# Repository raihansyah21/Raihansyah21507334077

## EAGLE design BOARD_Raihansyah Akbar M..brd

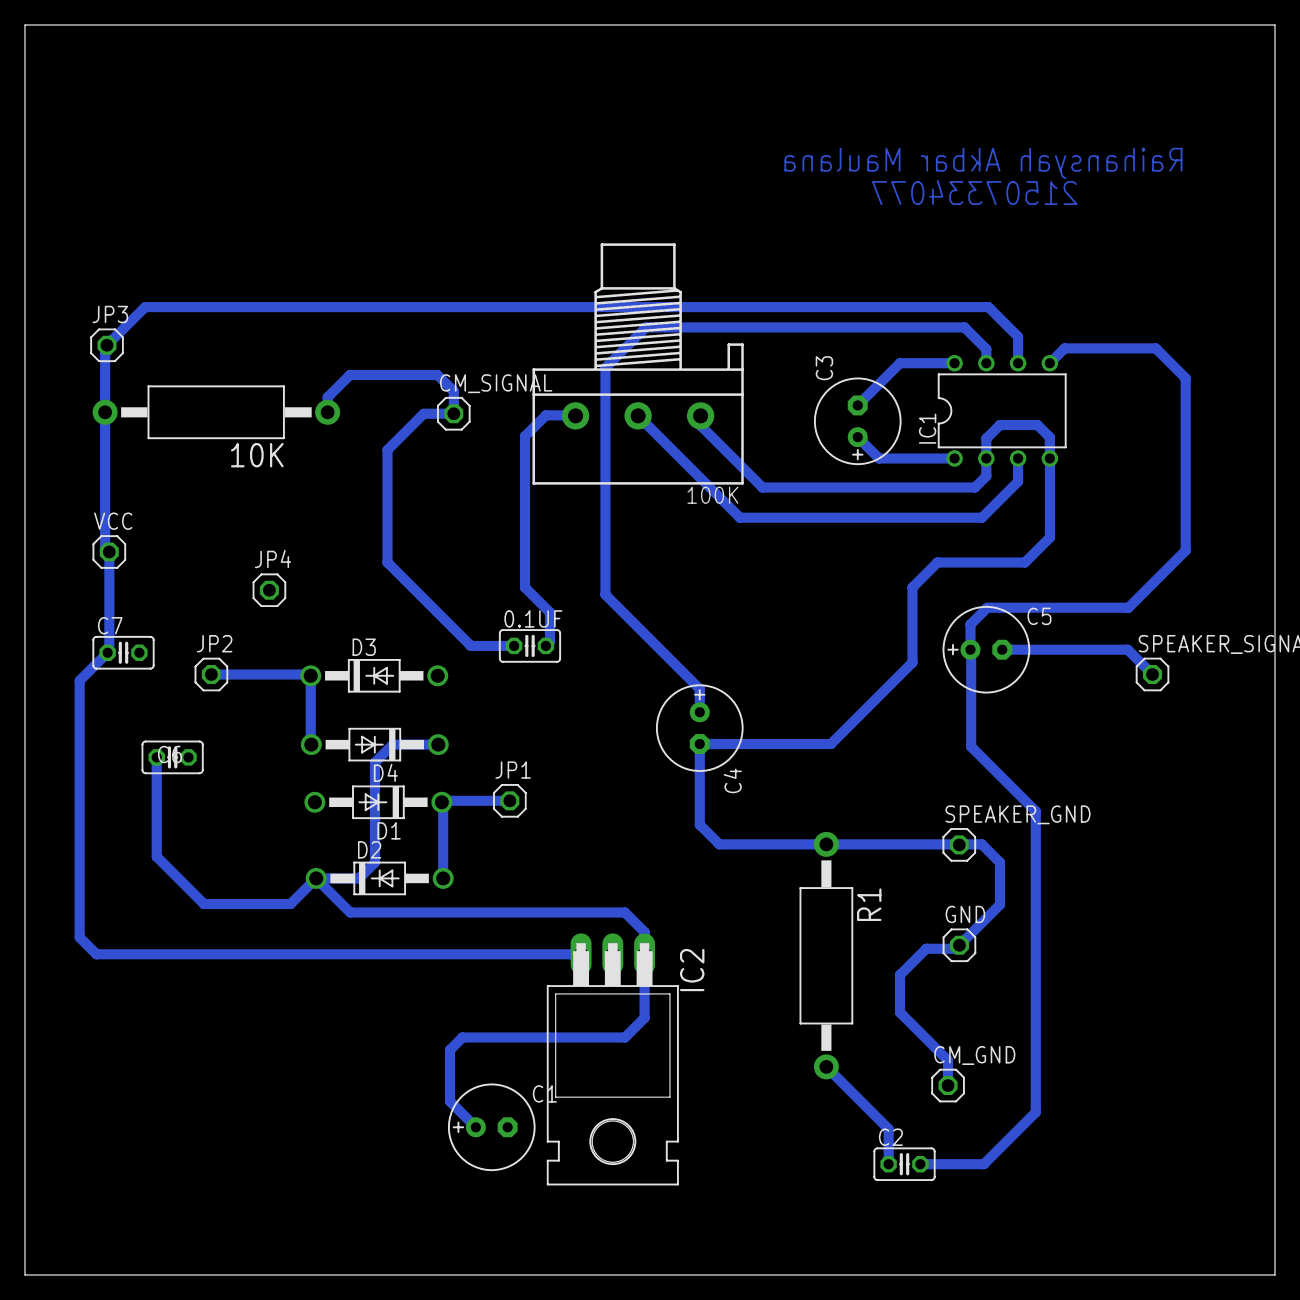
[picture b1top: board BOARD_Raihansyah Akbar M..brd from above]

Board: 2 copper layers, 100.0 x 100.0 mm, 27 parts (0 on the bottom side), 15 nets.

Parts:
0.1UF: C025-025X050
10K: AC01
100K: 3RP/1610N
C1: 470nF; E2,5-7
C2: C025-025X050
C3, C4, C5: E2,5-7
C6, C7: 100nF; C025-025X050
CM_GND: 1X01
CM_SIGNAL: 1X01
D1, D2, D3, D4: 1N4004; DO41-10
GND: 1X01
IC1: LM386N-3; DIL08
IC2: 7805T; TO220H
JP1: 9V trafo; 1X01
JP2: 0 trafo; 1X01
JP3: 5V; 1X01
JP4: GND; 1X01
R1: AC01
SPEAKER_GND: 1X01
SPEAKER_SIGNAL: 1X01
VCC: 1X01

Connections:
ABC: C1.-, C6.2, C7.2, D1.A, D3.A, IC2.2, JP4.1
unnamed: 0.1UF.1, 10K.1, CM_SIGNAL.1
unnamed: C3.+, IC1.1
unnamed: 0.1UF.2, 100K.3
unnamed: C3.-, IC1.8
unnamed: C2.2, C5.+, IC1.5
unnamed: 100K.2, IC1.3
unnamed: C2.1, R1.2
unnamed: C4.+, IC1.7
unnamed: D1.C, D2.A, JP1.1
unnamed: C1.+, C6.1, D2.C, D4.C, IC2.1
unnamed: D3.C, D4.A, JP2.1
SPEAKER_GND: 100K.1, C4.-, CM_GND.1, GND.1, IC1.2, IC1.4, R1.1, SPEAKER_GND.1
SPEAKER_SIGNAL: C5.-, SPEAKER_SIGNAL.1
VCC: 10K.2, C7.1, IC1.6, IC2.3, JP3.1, VCC.1

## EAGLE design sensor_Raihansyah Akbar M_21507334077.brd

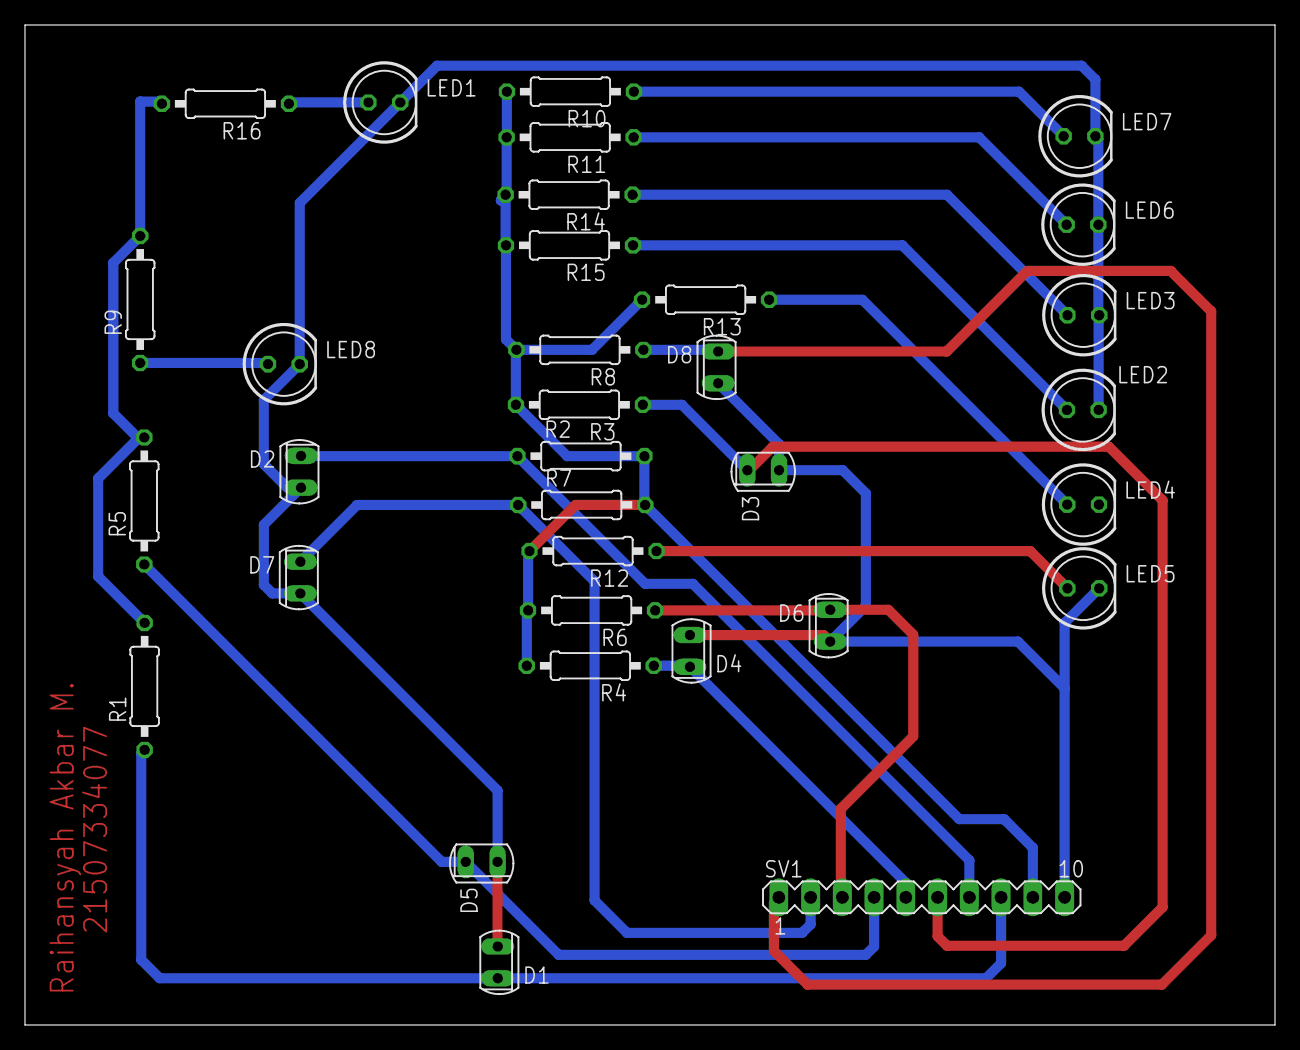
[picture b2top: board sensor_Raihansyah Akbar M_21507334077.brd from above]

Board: 2 copper layers, 100.0 x 80.0 mm, 33 parts (0 on the bottom side), 18 nets.

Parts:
D1, D2, D3, D4, D5, D6, D7, D8: PhotoDioda; SFH225
LED1, LED2, LED3, LED4, LED5, LED6, LED7, LED8: LED putih SB; LED5MM
R1, R2, R3, R4, R5, R6, R7, R8: 0207/10
R9, R10, R11, R12, R13, R14, R15, R16: 330; 0207/10
SV1: MA10-1

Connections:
GND: D1.A, D2.A, D3.A, D4.A, D5.A, D6.A, D7.A, D8.A, LED1.K, LED2.K, LED3.K, LED4.K, LED5.K, LED6.K, LED7.K, LED8.K, SV1.10
unnamed: LED7.A, R10.1
unnamed: D7.K, R7.1, SV1.2
unnamed: D8.K, R8.1, SV1.1
unnamed: D1.K, R1.1, SV1.8
unnamed: D2.K, R2.1, SV1.7
unnamed: D3.K, R3.1, SV1.6
unnamed: D5.K, R5.1, SV1.4
unnamed: D4.K, R4.1, SV1.5
unnamed: D6.K, R6.1, SV1.3
unnamed: LED6.A, R11.1
unnamed: LED5.A, R12.1
unnamed: LED4.A, R13.1
unnamed: LED3.A, R14.1
unnamed: LED2.A, R15.1
unnamed: LED1.A, R16.1
unnamed: LED8.A, R9.1
VCC: R1.2, R2.2, R3.2, R4.2, R5.2, R6.2, R7.2, R8.2, R9.2, R10.2, R11.2, R12.2, R13.2, R14.2, R15.2, R16.2, SV1.9

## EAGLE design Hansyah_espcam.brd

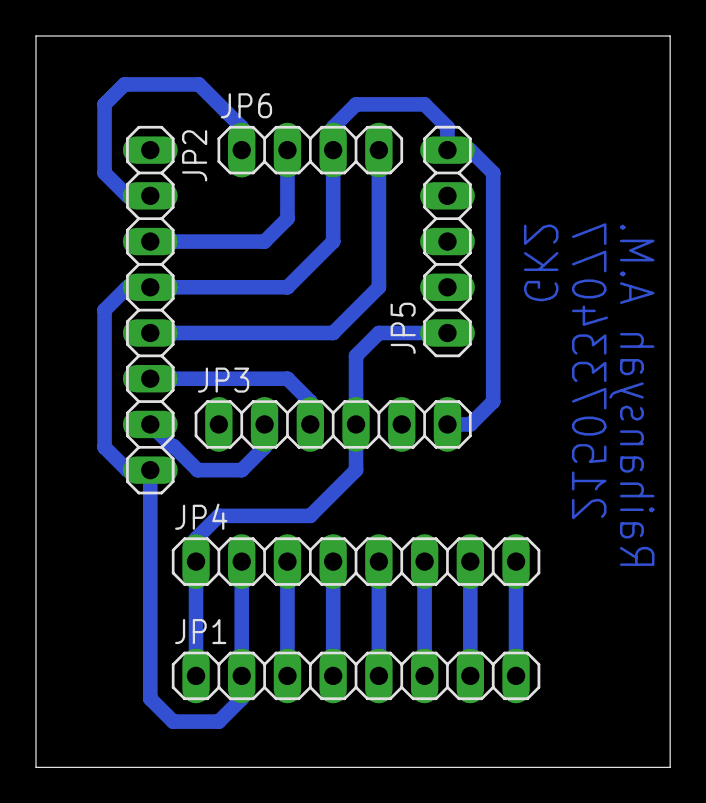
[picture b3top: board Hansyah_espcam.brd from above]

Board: 2 copper layers, 35.2 x 40.6 mm, 6 parts (0 on the bottom side), 13 nets.

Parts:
JP1, JP2, JP4: 1X08
JP3: 1X06
JP5: 1X05
JP6: 1X04

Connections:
5V: JP1.1, JP3.4, JP4.1, JP5.1
GND: JP1.2, JP2.4, JP2.8, JP3.6, JP4.2, JP5.5, JP6.3
IO0: JP2.3, JP6.2
IO2: JP1.7, JP4.7
IO4: JP1.8, JP4.8
IO12: JP1.3, JP4.3
IO13: JP1.4, JP4.4
IO14: JP1.6, JP4.6
IO15: JP1.5, JP4.5
IO16: JP2.2, JP6.1
RX: JP2.7, JP3.2
TX: JP2.6, JP3.3
VOUT: JP2.5, JP6.4

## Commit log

2021-09-27 Create Pensolderan pada Kabel
